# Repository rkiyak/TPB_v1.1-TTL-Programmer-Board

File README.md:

# TTL Programming Board (TPB v1.1)

This README file provides an introduction and usage guide for your TTL programming board. This board is designed for programming ESP32 boards using the CH340 TTL converter IC.

## Features

- Equipped with the CH340 TTL converter IC for programming ESP32 boards.
- Simple interface for quick and easy use.
- PCB design and connection schematics are provided.

## Connections

### Input Connector (Type-C)
- Input Voltage: 5V

### Programming Connector
The programming connector is used for programming ESP32 boards and has the following pin connections:

1. 3V3
2. TX
3. IO0
4. RX
5. GND
6. EN

These connections define the pins used for programming your ESP32 board. Please make sure to carefully connect to these pins for the programming process.

## Using the Board

Using the board is straightforward. You can program your ESP32 boards by following these steps:

1. Plug the board into the USB port.

2. Connect your ESP32 board to the TTL connection points on the board, ensuring that you follow the connection schematics.

3. Prepare your ESP32 program using Arduino IDE or a similar software.

4. Select the board and upload your program using Arduino IDE or your preferred software.

5. Once the programming process is complete, your ESP32 board is ready for use.

## Images

### Schematic

You can find the connection schematics for the board in the image below:

### PCB Images

Below are some images of the board's PCB design:

### 3D Images

Here are 3D images of the board:

## Support

If you have any questions or need assistance with using the board, please contact us at rk@rkiyak.com.

## License

The design of this board is licensed under the Open Source license. Please review the license document and ensure compliance before using the board.

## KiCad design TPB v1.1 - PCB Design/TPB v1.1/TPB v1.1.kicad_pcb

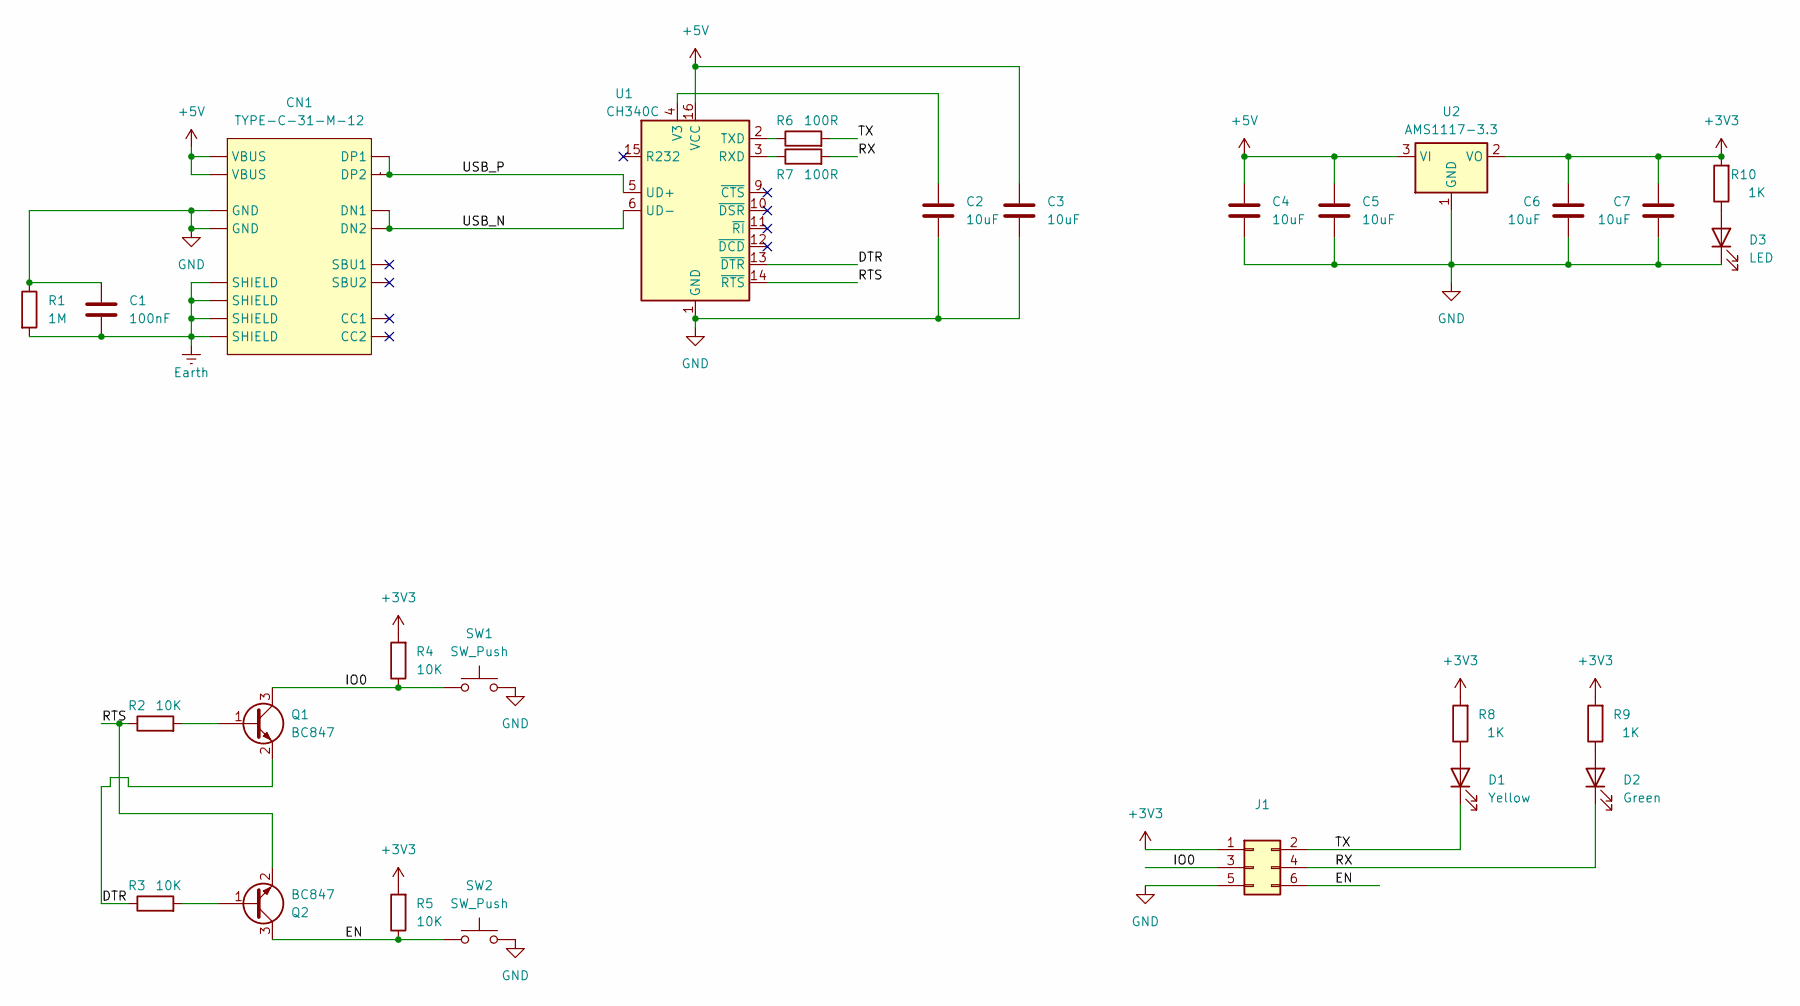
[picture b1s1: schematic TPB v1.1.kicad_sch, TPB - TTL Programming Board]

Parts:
C1: 100nF; C_0603_1608Metric_Pad1.08x0.95mm_HandSolder; Voltage 50V
C2, C3, C4, C5, C6, C7: 10uF; C_0603_1608Metric_Pad1.08x0.95mm_HandSolder
CN1: TYPE-C-31-M-12
D1: Yellow; LED_0805_2012Metric_Pad1.15x1.40mm_HandSolder
D2: Green; LED_0805_2012Metric_Pad1.15x1.40mm_HandSolder
D3: LED; LED_0805_2012Metric_Pad1.15x1.40mm_HandSolder
J1: IDC-Header_2x03_P2.54mm_Vertical
Q1, Q2: BC847; SOT-23
R1: 1M; R_0603_1608Metric_Pad0.98x0.95mm_HandSolder
R2, R3, R4, R5: 10K; R_0603_1608Metric_Pad0.98x0.95mm_HandSolder
R6, R7: 100R; R_0603_1608Metric_Pad0.98x0.95mm_HandSolder
R8, R9: 1K; R_0603_1608Metric_Pad0.98x0.95mm_HandSolder
R10: 1K; LED_0805_2012Metric_Pad1.15x1.40mm_HandSolder
SW1, SW2: SW_Push; SW_SPST_TL3305C
U1: CH340C; SOIC-16_3.9x9.9mm_P1.27mm
U2: AMS1117-3.3; SOT-223-3_TabPin2

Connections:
+3V3: C6.1, C7.1, J1.1, R4.2, R5.2, R8.2, R9.2, R10.2, U2.2 (VO)
+5V: C3.1, C4.1, C5.1, CN1.A4/B9 (VBUS), CN1.B4/A9 (VBUS), U1.16 (VCC), U2.3 (VI)
/DTR: Q1.2 (E), R3.1, U1.13 (~DTR)
/EN: J1.6, Q2.3 (C), R5.1, SW2.1
/IO0: J1.3, Q1.3 (C), R4.1, SW1.1
/RTS: Q2.2 (E), R2.1, U1.14 (~RTS)
/RX: D2.1 (K), J1.4, R7.2
/TX: D1.1 (K), J1.2, R6.2
/USB_N: CN1.A7 (DN1), CN1.B7 (DN2), U1.6 (UD-)
/USB_P: CN1.A6 (DP1), CN1.B6 (DP2), U1.5 (UD+)
Earth: C1.2, CN1.S1 (SHIELD), CN1.S2 (SHIELD), CN1.S3 (SHIELD), CN1.S4 (SHIELD), R1.2
GND: C1.1, C2.2, C3.2, C4.2, C5.2, C6.2, C7.2, CN1.A1/B12 (GND), CN1.B1/A12 (GND), D3.1 (K), J1.5, R1.1, SW1.2, SW2.2, U1.1 (GND), U2.1 (GND)
unnamed: D1.2 (A), R8.1
unnamed: D2.2 (A), R9.1
unnamed: D3.2 (A), R10.1
unnamed: Q1.1 (B), R2.2
unnamed: Q2.1 (B), R3.2
unnamed: R7.1, U1.3 (RXD)
unnamed: R6.1, U1.2 (TXD)
unnamed: C2.1, U1.4 (V3)

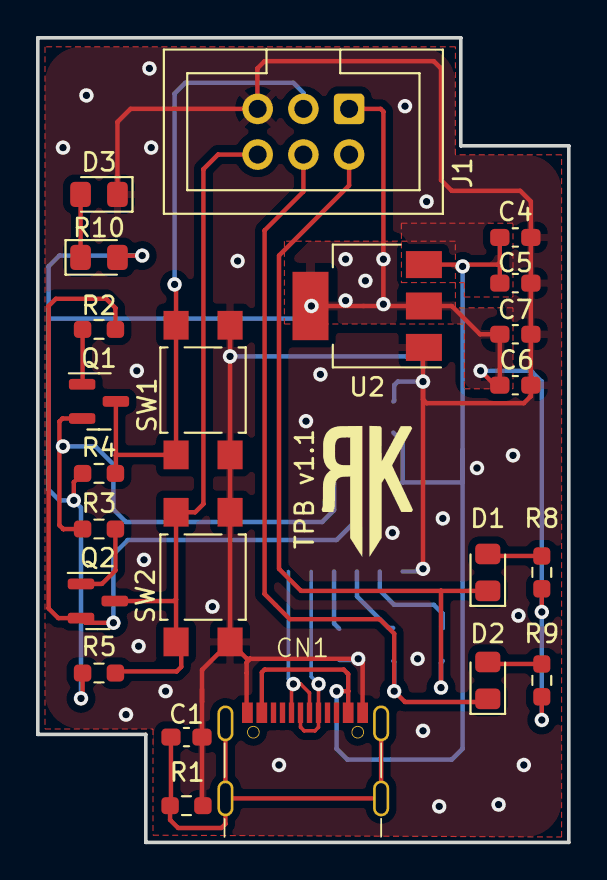
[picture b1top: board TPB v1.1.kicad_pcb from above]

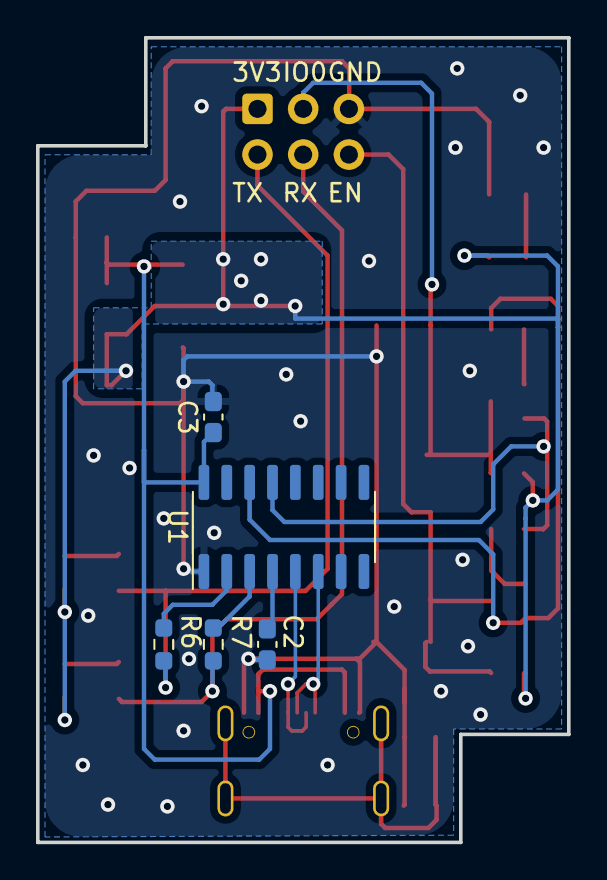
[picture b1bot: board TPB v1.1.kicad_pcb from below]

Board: 2 copper layers, 29.5 x 44.7 mm, 28 parts (5 on the bottom side), 20 nets.

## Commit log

2023-09-10 PCB Directory Created
2023-09-11 Kicad Project Created
2023-09-15 Schematic v1
2023-09-16 Schematic v2
2023-09-18 PCB Layout v1
2023-09-19 Board Outline, Polygon and 3D of Buttons Added
2023-09-19 Pcb Design Complated
2023-09-20 DRC Errs Solved
2023-09-20 Gerber Files Created
2023-10-06 readMe and Photos Added
2024-01-12 USB Type C connector 3D Fixed
